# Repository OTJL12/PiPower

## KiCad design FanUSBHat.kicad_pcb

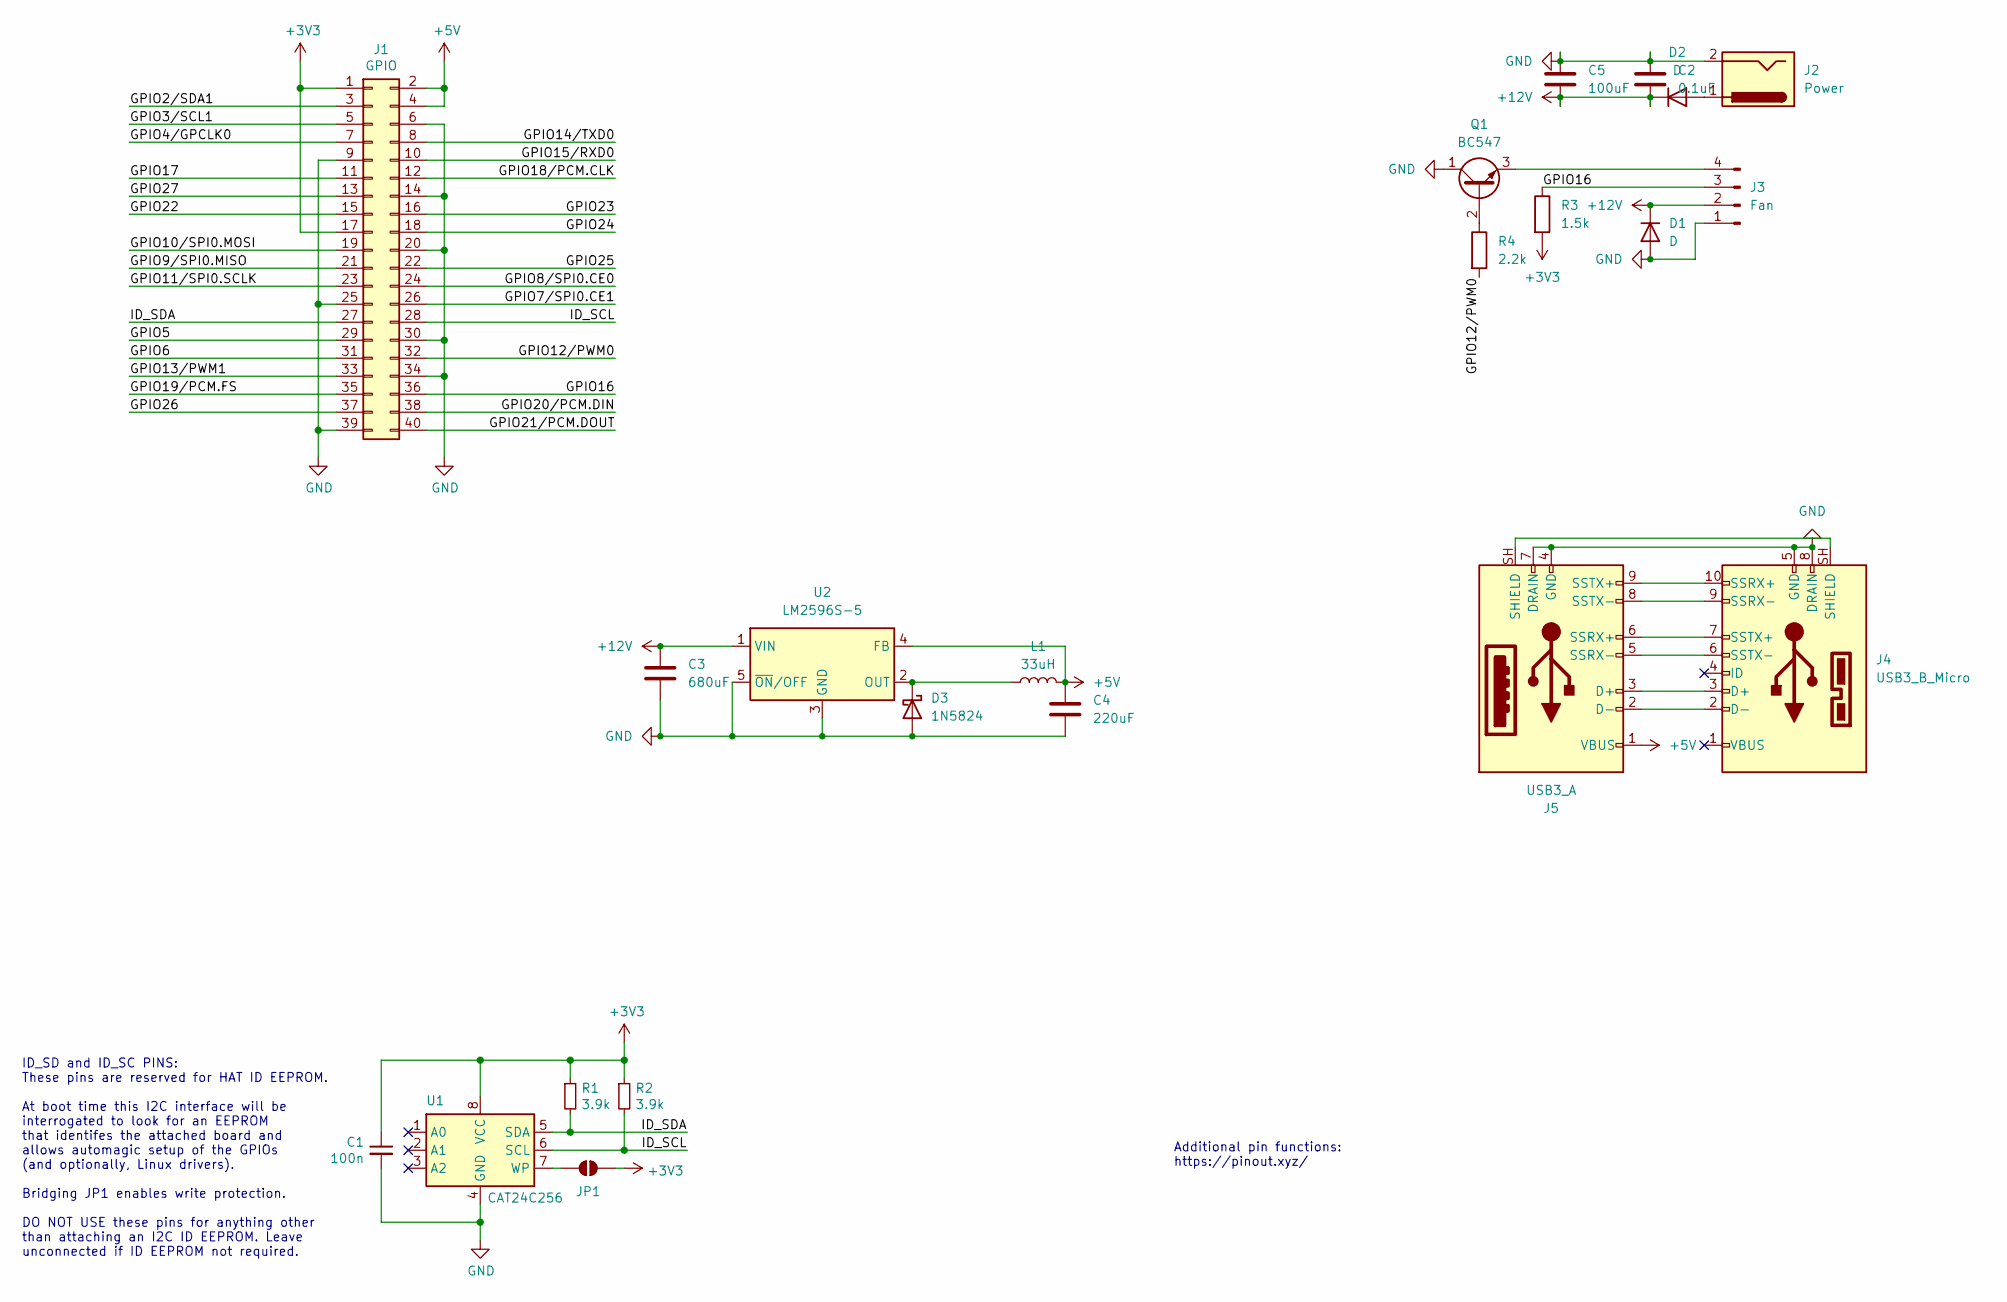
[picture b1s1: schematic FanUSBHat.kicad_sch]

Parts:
C1: 100n; C_0805_2012Metric_Pad1.18x1.45mm_HandSolder
C2: 0.1uF; C_0805_2012Metric_Pad1.18x1.45mm_HandSolder
C3: 680uF; C_Elec_10x10.2
C4: 220uF; C_Elec_6.3x7.7
C5: 100uF; C_Elec_6.3x7.7
D1, D2: D; D_SMA
D3: 1N5824; D_DO-201AD_P15.24mm_Horizontal
J1: GPIO; PinSocket_2x20_P2.54mm_Vertical
J2: Power; BarrelJack_Horizontal
J3: Fan; FanPinHeader_1x04_P2.54mm_Vertical
J4: USB3_B_Micro; USB3_Micro-B_Connfly_DS1104-01
J5: USB3_A; USB3_A_Molex_48393-001
JP1: ID_WP; SolderJumper-2_P1.3mm_Open_RoundedPad1.0x1.5mm
L1: 33uH; L_12x12mm_H8mm
Q1: BC547; TO-92_Inline
R1, R2: 3.9k; R_0805_2012Metric
R3: 1.5k; R_0805_2012Metric
R4: 2.2k; R_0805_2012Metric
U1: CAT24C256; SOIC-8_3.9x4.9mm_P1.27mm
U2: LM2596S-5; TO-263-5_TabPin3

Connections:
+3V3: C1.1, J1.1, J1.17, JP1.2 (B), R1.1, R2.1, R3.2, U1.8 (VCC)
+5V: C4.1, J1.2, J1.4, J5.1 (VBUS), L1.2, U2.4 (FB)
+12V: C2.2, C3.1, C5.2, D1.1 (K), D2.1 (K), J3.2, U2.1 (VIN)
/GPIO2/SDA1: J1.3
/GPIO3/SCL1: J1.5
/GPIO4/GPCLK0: J1.7
/GPIO5: J1.29
/GPIO6: J1.31
/GPIO7/SPI0.CE1: J1.26
/GPIO8/SPI0.CE0: J1.24
/GPIO9/SPI0.MISO: J1.21
/GPIO10/SPI0.MOSI: J1.19
/GPIO11/SPI0.SCLK: J1.23
/GPIO12/PWM0: J1.32, R4.2
/GPIO13/PWM1: J1.33
/GPIO14/TXD0: J1.8
/GPIO15/RXD0: J1.10
/GPIO16: J1.36, J3.3, R3.1
/GPIO17: J1.11
/GPIO18/PCM.CLK: J1.12
/GPIO19/PCM.FS: J1.35
/GPIO20/PCM.DIN: J1.38
/GPIO21/PCM.DOUT: J1.40
/GPIO22: J1.15
/GPIO23: J1.16
/GPIO24: J1.18
/GPIO25: J1.22
/GPIO26: J1.37
/GPIO27: J1.13
/ID_SCL: J1.28, R2.2, U1.6 (SCL)
/ID_SDA: J1.27, R1.2, U1.5 (SDA)
GND: C1.2, C2.1, C3.2, C4.2, C5.1, D1.2 (A), D3.2 (A), J1.6, J1.9, J1.14, J1.20, J1.25, J1.30, J1.34, J1.39, J2.2, J3.1, J4.5 (GND), J4.8 (DRAIN), J5.4 (GND), J5.7 (DRAIN), Q1.1 (C), U1.4 (GND), U2.3 (GND), U2.5 (~ON/OFF)
unnamed: D2.2 (A), J2.1
unnamed: D3.1 (K), L1.1, U2.2 (OUT)
unnamed: J3.4, Q1.3 (E)
unnamed: J4.3 (D+), J5.3 (D+)
unnamed: J4.2 (D-), J5.2 (D-)
unnamed: J4.SH (SHIELD), J5.SH (SHIELD)
unnamed: J4.10 (SSRX+), J5.9 (SSTX+)
unnamed: J4.9 (SSRX-), J5.8 (SSTX-)
unnamed: J4.7 (SSTX+), J5.6 (SSRX+)
unnamed: J4.6 (SSTX-), J5.5 (SSRX-)
unnamed: JP1.1 (A), U1.7 (WP)
unnamed: Q1.2 (B), R4.1

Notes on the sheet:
Additional pin functions: https://pinout.xyz/
ID_SD and ID_SC PINS: These pins are reserved for HAT ID EEPROM. At boot time this I2C interface will be interrogated to look for an EEPROM that identifes the attached board and allows automagic setup of the GPIOs (and optionally, Linux drivers). Bridging JP1 enables write protection. DO NOT USE th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

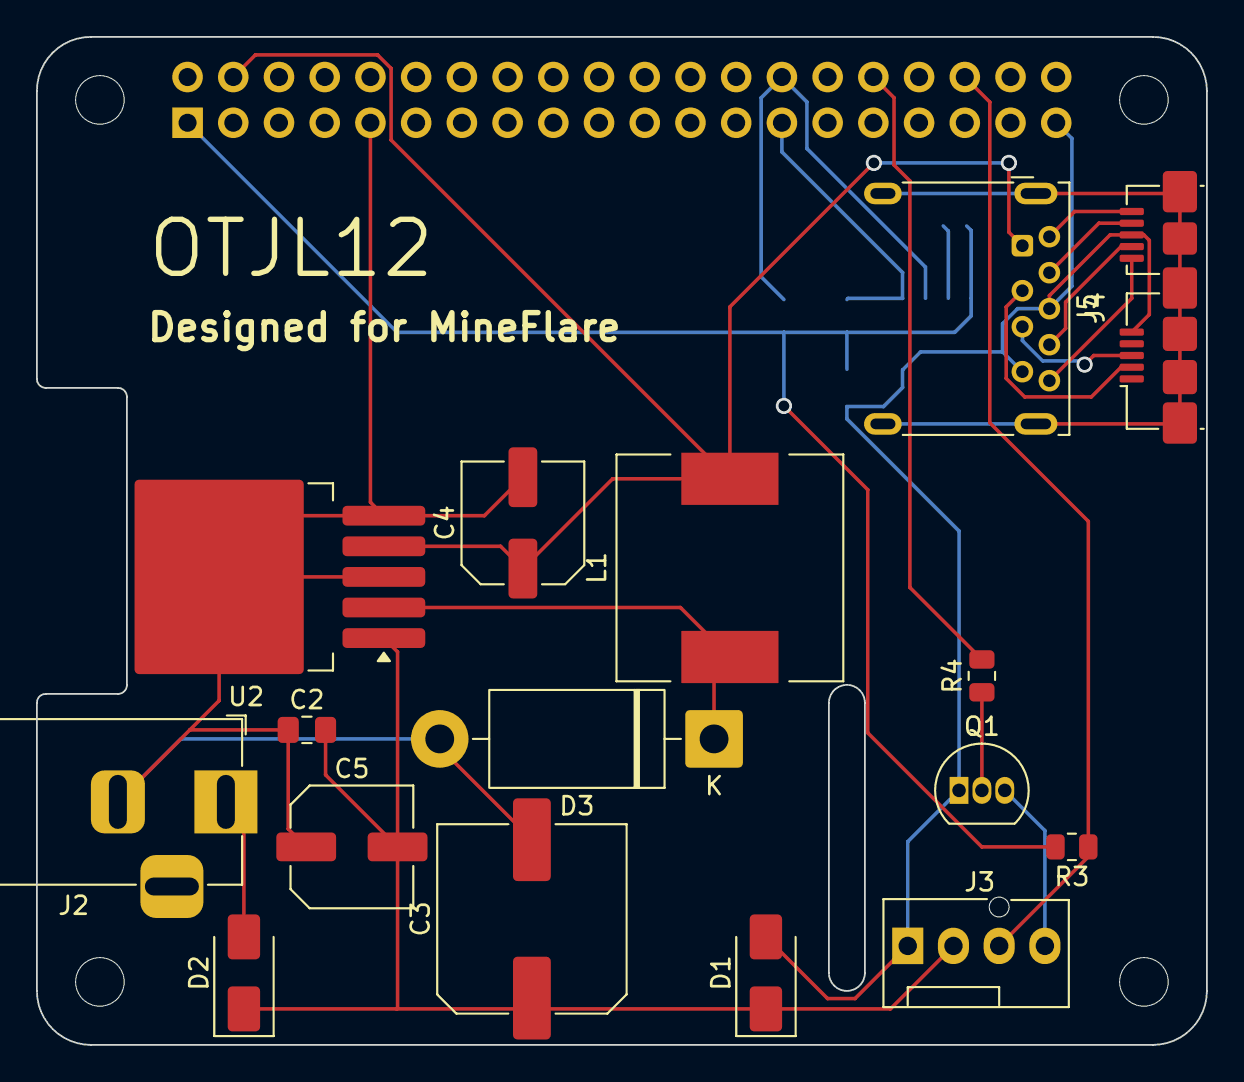
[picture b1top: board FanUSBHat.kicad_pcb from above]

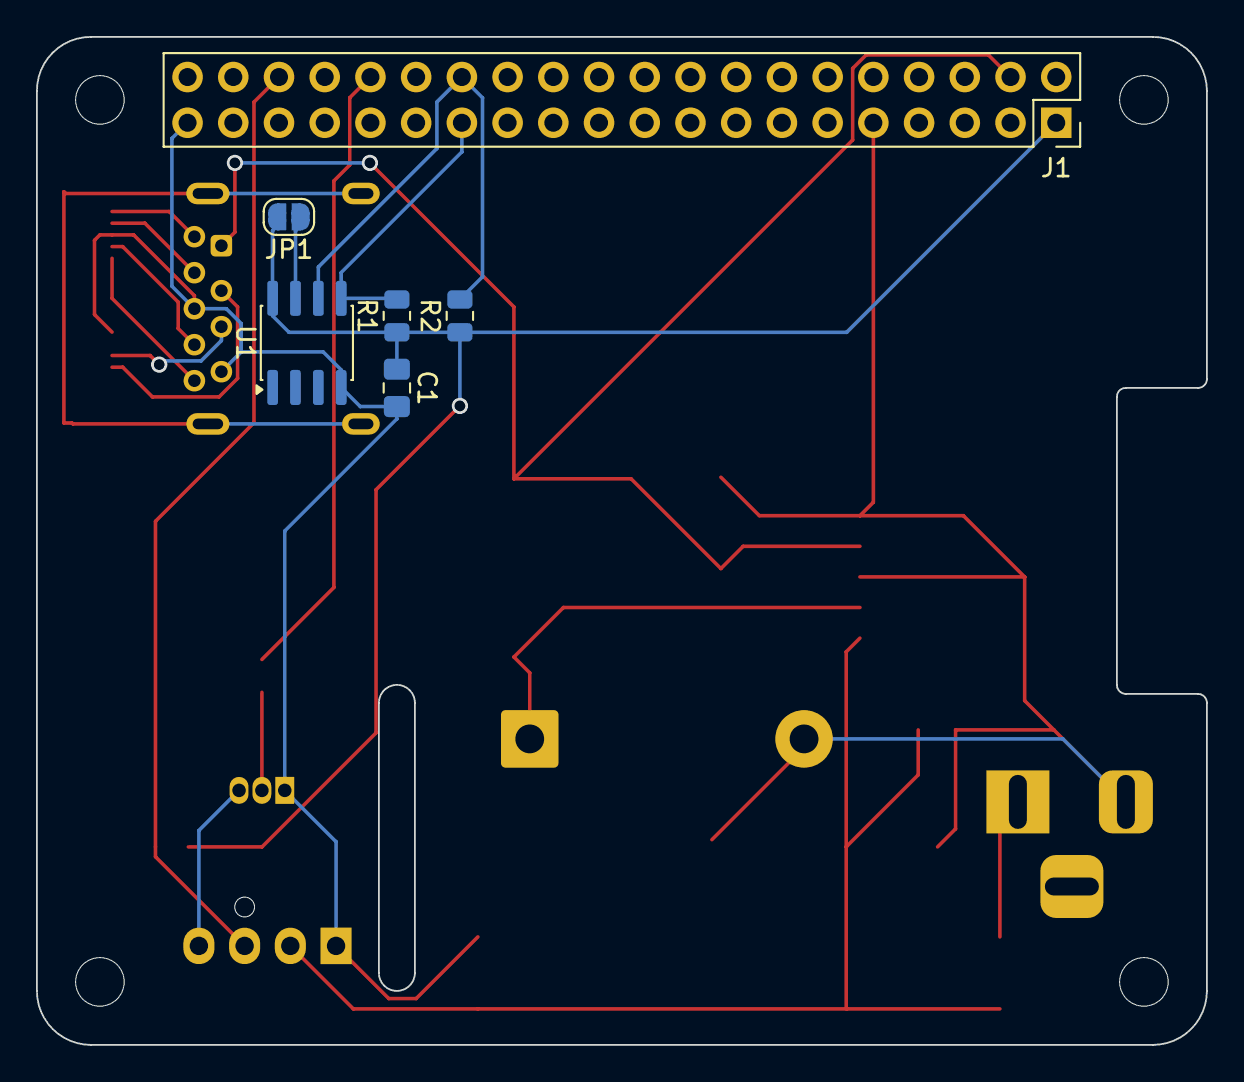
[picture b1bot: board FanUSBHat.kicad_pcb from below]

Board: 2 copper layers, 65.0 x 56.0 mm, 26 parts (6 on the bottom side), 20 nets.

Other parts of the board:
MH1, MH2, MH3, MH4: MountingHole_2.7mm_M2.5
